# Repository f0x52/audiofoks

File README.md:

# MusikFoks
Little addon board for the [USBCWrover](https://github.com/sebastius/USBCWrover), connecting a MSEQ7 graphic equalizer chip.  
Can be used in combination with something like [ESP32 FFT Audio LEDS](https://github.com/debsahu/ESP32_FFT_Audio_LEDs)

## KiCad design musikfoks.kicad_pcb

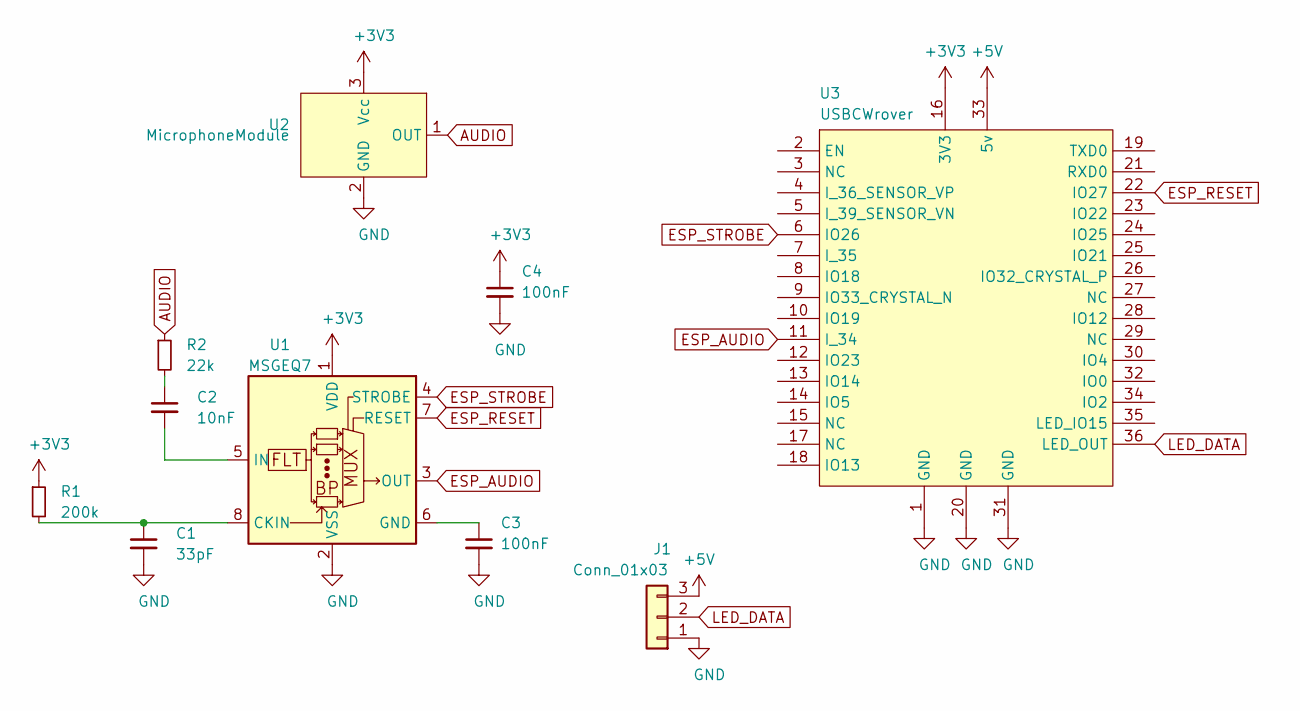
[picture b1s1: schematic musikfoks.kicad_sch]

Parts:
C1: 33pF; C_0603_1608Metric
C2: 10nF; C_0603_1608Metric
C3, C4: 100nF; C_0603_1608Metric
J1: Conn_01x03; PinSocket_1x03_P2.54mm_Vertical
R1: 200k; R_0603_1608Metric
R2: 22k; R_0603_1608Metric
U1: MSGEQ7; DIP-8_W7.62mm
U2: MicrophoneModule
U3: USBCWrover

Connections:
+3V3: C4.1, R1.1, U1.1 (VDD), U2.3 (Vcc), U3.16 (3V3)
+5V: J1.3, U3.33 (5v)
AUDIO: R2.1, U2.1 (OUT)
ESP_AUDIO: U1.3 (OUT), U3.11 (I_34)
ESP_RESET: U1.7 (RESET), U3.22 (IO27)
ESP_STROBE: U1.4 (STROBE), U3.6 (IO26)
GND: C1.2, C3.2, C4.2, J1.1, U1.2 (VSS), U2.2 (GND), U3.1 (GND), U3.20 (GND), U3.31 (GND)
LED_DATA: J1.2, U3.36 (LED_OUT)
unnamed: C1.1, R1.2, U1.8 (CKIN)
unnamed: C2.1, R2.2
unnamed: C2.2, U1.5 (IN)
unnamed: C3.1, U1.6 (GND)

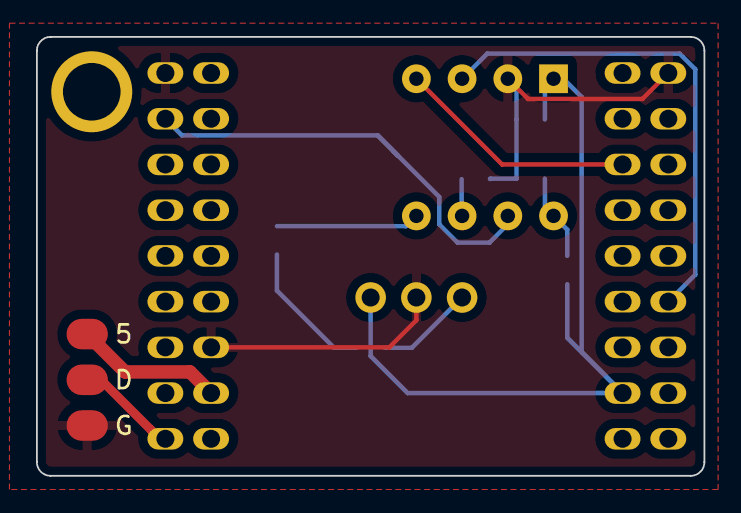
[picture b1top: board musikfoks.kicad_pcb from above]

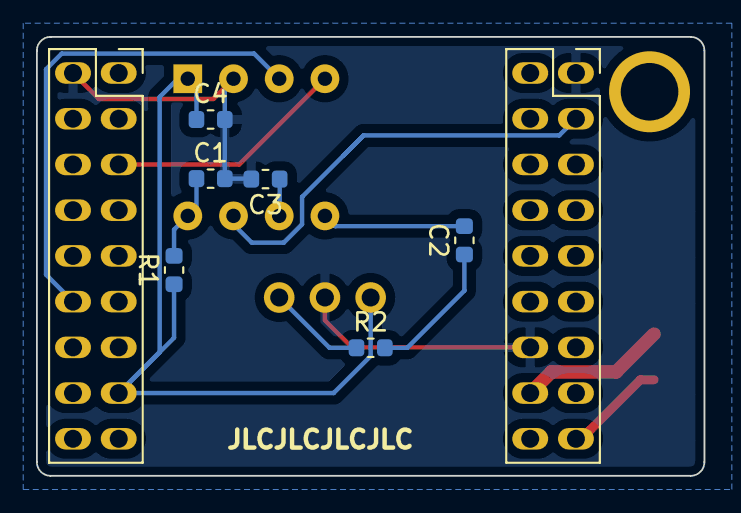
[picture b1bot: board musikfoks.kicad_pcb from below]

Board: 2 copper layers, 37.1 x 24.4 mm, 10 parts (7 on the bottom side), 12 nets.

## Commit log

2020-09-08 initial commit, waiting for final art
2020-09-13 update art
2020-09-13 rename to musikfoks
2020-09-13 readme, render
2020-09-13 GPL-3.0
